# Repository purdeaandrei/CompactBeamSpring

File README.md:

# Compact Beamspring controller.

This controller only supports new style card edge connectors only, and it requires the side
of the card edge connector to be cut off, and the pins be bent 90 degress.

## Images

## Other controllers in this family:
* https://github.com/purdeaandrei/CompactBeamSpringAdditionalExpansion
* https://github.com/purdeaandrei/SMDModelFController
* https://github.com/purdeaandrei/SMDModelFController/tree/extra_columns
* https://github.com/purdeaandrei/SMD4704KishsaverClassModelFController
* https://github.com/listofoptions/TH-XWhatsIt

## Origins and license

This project is based on the Through-hole xwhatsit by listofoptions, which is un turn
based on the capsense controllers by XWhatsIt
(Tom Wong-Cornall). original liscencure holds, as well as CERN OSH
(compatible license).

original implementation of Tom Wong-Cornall's controller documented here

http://downloads.cornall.co/ibm-capsense-usb-web/ibm-capsense-usb.html

Working theory of operation is under the previous link.

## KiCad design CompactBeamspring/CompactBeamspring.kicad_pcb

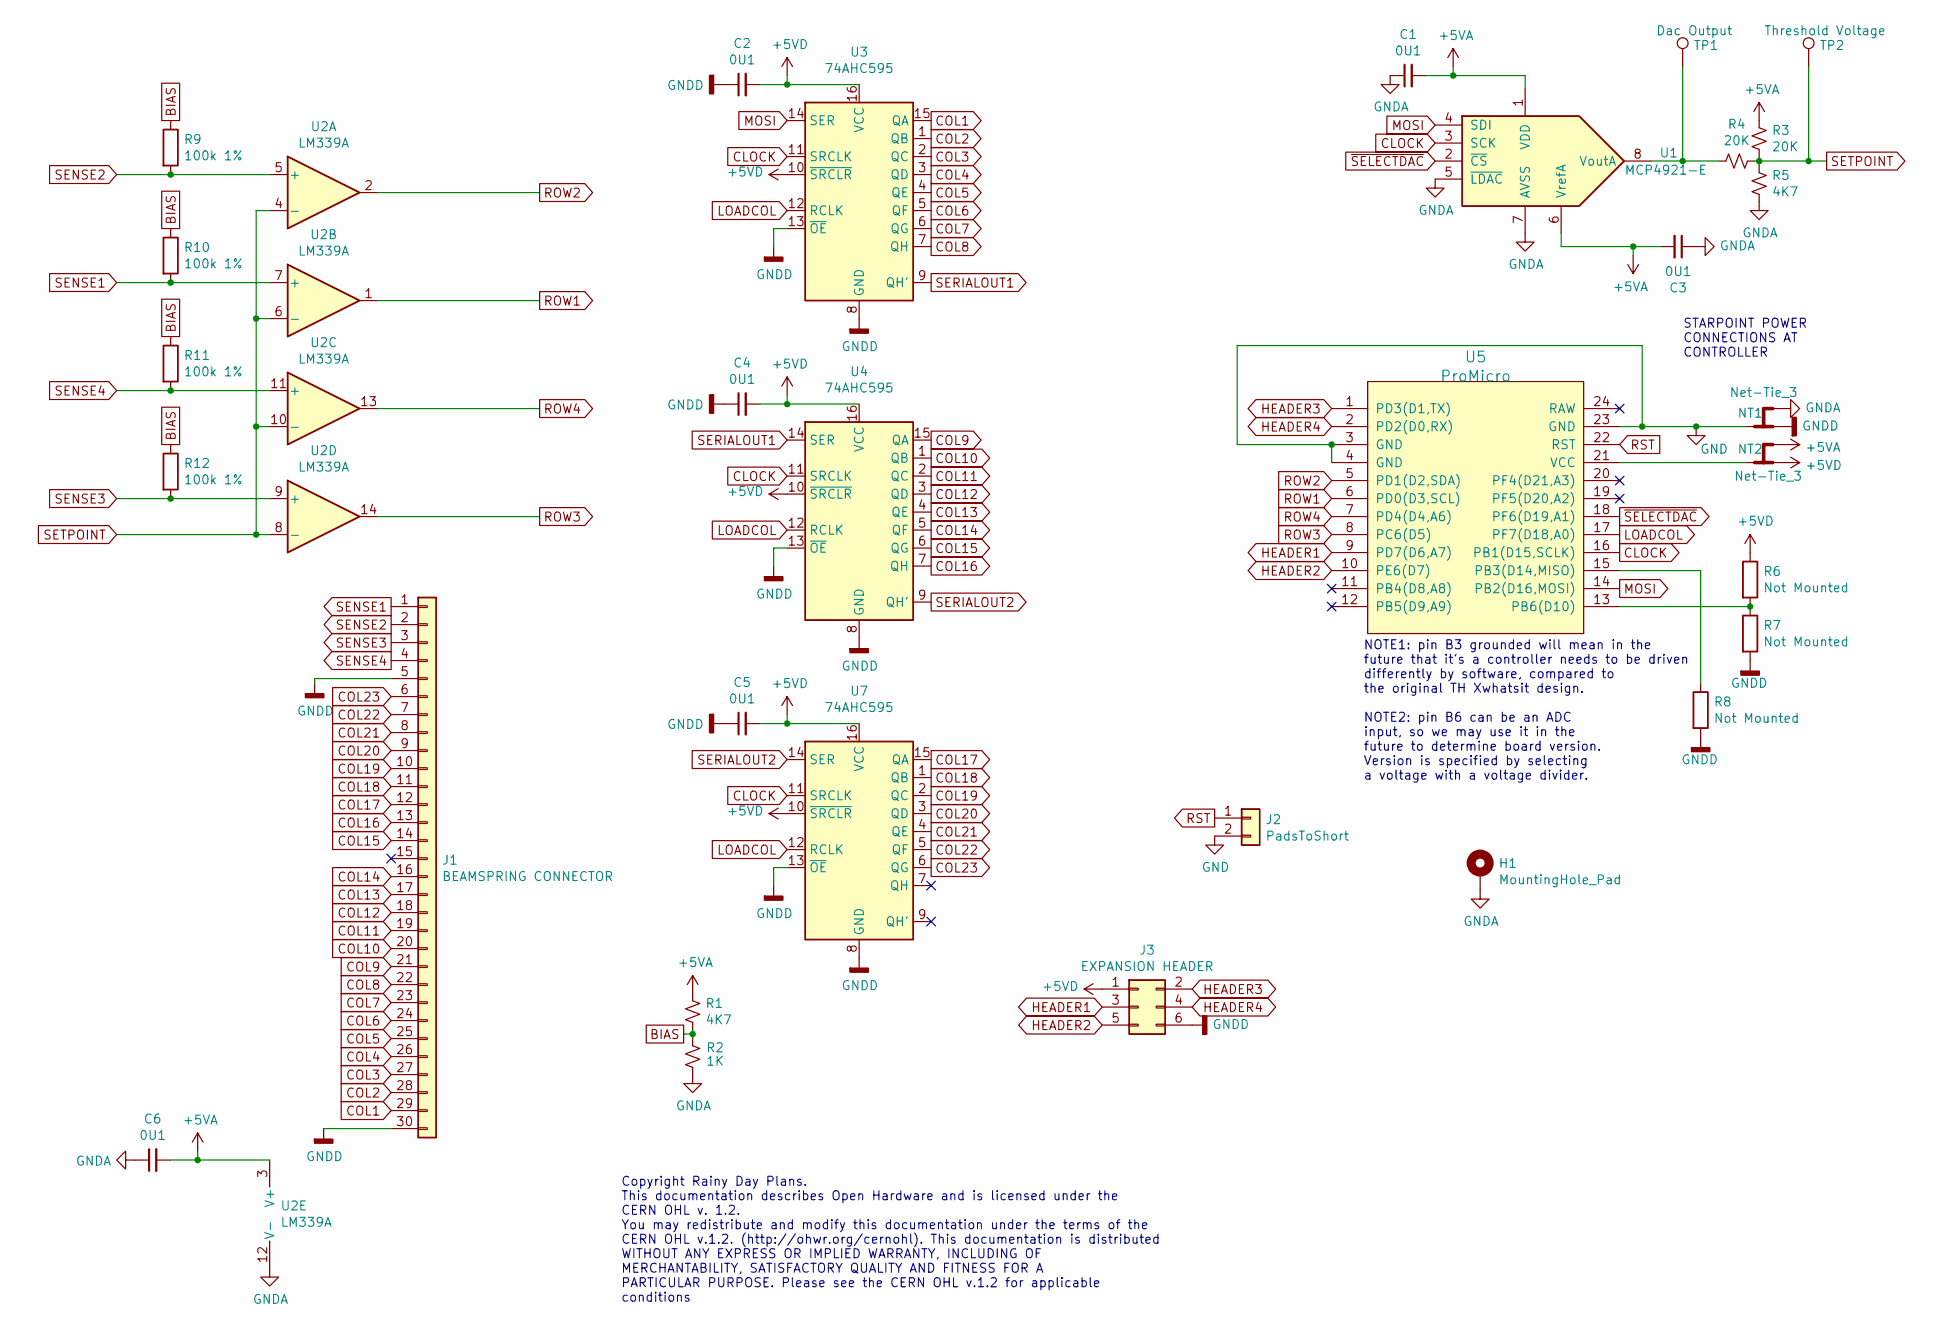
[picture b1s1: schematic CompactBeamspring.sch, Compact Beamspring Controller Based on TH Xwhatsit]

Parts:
C1, C2, C3, C4, C5, C6: 0U1; C_0805_2012Metric_Pad1.15x1.40mm_HandSolder; LCSC C49678
H1: MountingHole_Pad; ChassisGnd
J1: BEAMSPRING CONNECTOR; 30-pin-universal-beamspring-connector_v3_onlyflat
J2: PadsToShort
J3: EXPANSION HEADER; PinHeader_2x03_P2.54mm_Vertical
NT1, NT2: Net-Tie_3; NetTie-3_THT_Pad0.3mm
R1, R5: 4K7; R_0805_2012Metric_Pad1.15x1.40mm_HandSolder; LCSC C17673
R2: 1K; R_0805_2012Metric_Pad1.15x1.40mm_HandSolder; LCSC C17513
R3, R4: 20K; R_0805_2012Metric_Pad1.15x1.40mm_HandSolder; LCSC C4328
R6, R7, R8: Not Mounted; R_0805_2012Metric_Pad1.15x1.40mm_HandSolder
R9, R10, R11, R12: 100k 1%; R_0805_2012Metric_Pad1.15x1.40mm_HandSolder; LCSC C17407
TP1: Dac Output; TestPoint_Pad_D1.0mm
TP2: Threshold Voltage; TestPoint_Pad_D1.0mm
U1: MCP4921-E; SOIC-8_3.9x4.9mm_P1.27mm; LCSC C43499
U2: LM339A; SOIC-14_3.9x8.7mm_P1.27mm; LCSC C74559
U3, U4, U7: 74AHC595; SOIC-16_3.9x9.9mm_P1.27mm; LCSC C5520
U5: ProMicro

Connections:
+5VA: C1.2, C3.2, C6.2, NT2.3, R1.1, R3.2, U1.1 (VDD), U1.6 (VrefA), U2.3 (V+)
+5VD: C2.2, C4.2, C5.2, J3.1, NT2.1, R6.1, U3.10 (~SRCLR), U3.16 (VCC), U4.10 (~SRCLR), U4.16 (VCC), U7.10 (~SRCLR), U7.16 (VCC)
BIAS: R1.2, R2.2, R9.1, R10.1, R11.1, R12.1
CLOCK: U1.3 (SCK), U3.11 (SRCLK), U4.11 (SRCLK), U5.16 (PB1(D15,SCLK)), U7.11 (SRCLK)
COL1: J1.29, U3.15 (QA)
COL2: J1.28, U3.1 (QB)
COL3: J1.27, U3.2 (QC)
COL4: J1.26, U3.3 (QD)
COL5: J1.25, U3.4 (QE)
COL6: J1.24, U3.5 (QF)
COL7: J1.23, U3.6 (QG)
COL8: J1.22, U3.7 (QH)
COL9: J1.21, U4.15 (QA)
COL10: J1.20, U4.1 (QB)
COL11: J1.19, U4.2 (QC)
COL12: J1.18, U4.3 (QD)
COL13: J1.17, U4.4 (QE)
COL14: J1.16, U4.5 (QF)
COL15: J1.14, U4.6 (QG)
COL16: J1.13, U4.7 (QH)
COL17: J1.12, U7.15 (QA)
COL18: J1.11, U7.1 (QB)
COL19: J1.10, U7.2 (QC)
COL20: J1.9, U7.3 (QD)
COL21: J1.8, U7.4 (QE)
COL22: J1.7, U7.5 (QF)
COL23: J1.6, U7.6 (QG)
GND: J2.2, NT1.2, U5.3 (GND), U5.4 (GND), U5.23 (GND)
GNDA: C1.1, C3.1, C6.1, H1.1, NT1.3, R2.1, R5.1, U1.5 (~LDAC~), U1.7 (AVSS), U2.12 (V-)
GNDD: C2.1, C4.1, C5.1, J1.5, J1.30, J3.6, NT1.1, R7.2, R8.2, U3.8 (GND), U3.13 (~OE), U4.8 (GND), U4.13 (~OE), U7.8 (GND), U7.13 (~OE)
HEADER1: J3.3, U5.9 (PD7(D6,A7))
HEADER2: J3.5, U5.10 (PE6(D7))
HEADER3: J3.2, U5.1 (PD3(D1,TX))
HEADER4: J3.4, U5.2 (PD2(D0,RX))
LOADCOL: U3.12 (RCLK), U4.12 (RCLK), U5.17 (PF7(D18,A0)), U7.12 (RCLK)
MOSI: U1.4 (SDI), U3.14 (SER), U5.14 (PB2(D16,MOSI))
unnamed: NT2.2, U5.21 (VCC)
unnamed: R4.2, TP1.1, U1.8 (VoutA)
unnamed: R6.2, R7.1, U5.13 (PB6(D10))
unnamed: R8.1, U5.15 (PB3(D14,MISO))
ROW1: U2.1, U5.6 (PD0(D3,SCL))
ROW2: U2.2, U5.5 (PD1(D2,SDA))
ROW3: U2.14, U5.8 (PC6(D5))
ROW4: U2.13, U5.7 (PD4(D4,A6))
RST: J2.1, U5.22 (RST)
SENSE1: J1.1, R10.2, U2.7 (+)
SENSE2: J1.2, R9.2, U2.5 (+)
SENSE3: J1.3, R12.2, U2.9 (+)
SENSE4: J1.4, R11.2, U2.11 (+)
SERIALOUT1: U3.9 (QH'), U4.14 (SER)
SERIALOUT2: U4.9 (QH'), U7.14 (SER)
SETPOINT: R3.1, R4.1, R5.2, TP2.1, U2.4 (-), U2.6 (-), U2.8 (-), U2.10 (-)
~SELECTDAC: U1.2 (~CS~), U5.18 (PF6(D19,A1))

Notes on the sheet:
Copyright Rainy Day Plans. This documentation describes Open Hardware and is licensed under the CERN OHL v. 1.2. You may redistribute and modify this documentation under the terms of the CERN OHL v.1.2. (http://ohwr.org/cernohl). This documentation is distributed WITHOUT ANY EXPRESS OR IMPLIED WARR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
NOTE1: pin B3 grounded will mean in the future that it's a controller needs to be driven differently by software, compared to the original TH Xwhatsit design. NOTE2: pin B6 can be an ADC input, so we may use it in the future to determine board version. Version is specified by selecting a voltage wi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
STARPOINT POWER CONNECTIONS AT CONTROLLER

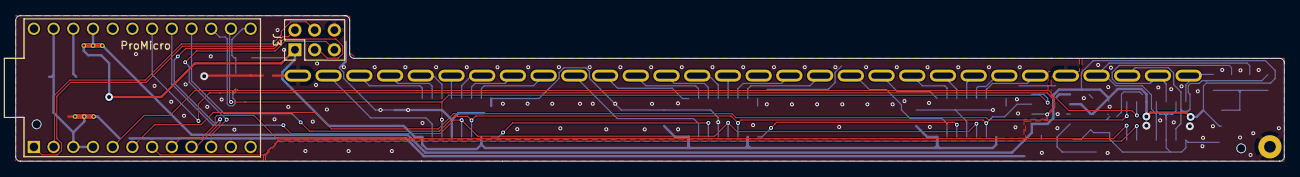
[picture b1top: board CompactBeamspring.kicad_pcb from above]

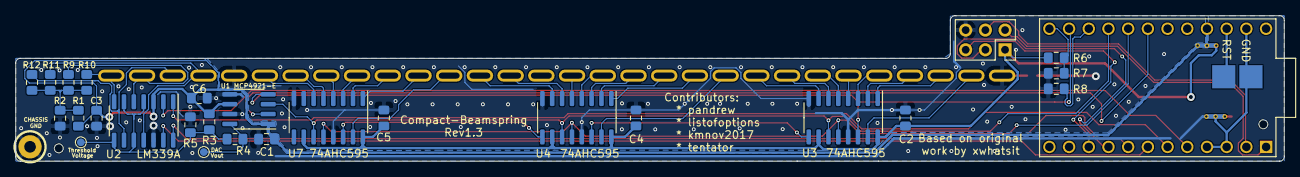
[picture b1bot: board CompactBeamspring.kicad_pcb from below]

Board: 2 copper layers, 163.6 x 18.8 mm, 32 parts (29 on the bottom side), 53 nets.

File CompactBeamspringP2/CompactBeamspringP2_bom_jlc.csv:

"Comment","Designator","Footprint","LCSC Part #"
"0U1","C2,C6,C5,C3,C1,C4","C_0805_2012Metric_Pad1.15x1.40mm_HandSolder","C49678"
"1K","R2","R_0805_2012Metric_Pad1.15x1.40mm_HandSolder","C17513"
"20K","R4,R3","R_0805_2012Metric_Pad1.15x1.40mm_HandSolder","C4328"
"4K7","R5,R1","R_0805_2012Metric_Pad1.15x1.40mm_HandSolder","C17673"
"100k 1%","R9,R10,R11,R12","R_0805_2012Metric_Pad1.15x1.40mm_HandSolder","C149504"
"MCP4921-E","U1","SOIC-8_3.9x4.9mm_P1.27mm","C43499"
"LM339A","U2","SOIC-14_3.9x8.7mm_P1.27mm","C74559"
"74AHC595","U3,U4,U7","SOIC-16_3.9x9.9mm_P1.27mm","C5520"

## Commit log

2020-08-16 Added compact beamspring-only version
2020-08-17 remove old gerber files
2020-08-17 added version selection resistor divider pads
2020-08-17 cleaned away some extra copper traces around pads connected to copper fills
2020-08-17 cleaned up cuts in the copper fill
2020-08-17 a bit more copper pour-related cleanups
2020-08-17 Added chassis ground, and added some silkscreen
2020-08-17 fixed net tie thermal relief
2020-08-17 moved chassis gnd connection a little in order to get 3 connections to gnd plane
2020-08-17 added copper fill keepout to shorted configuration resistor
2020-08-17 added forgotten chassis gnd footprint
2020-08-17 more tweaks: corners bigger radius, some more rework on traces, and copper fills
2020-08-17 added panelized pcb
2020-08-17 added tooling hole
2020-08-17 added tooling holes to existing panel
2020-08-17 single pcb: added tooling holes, position is only good for when pcbs are panelized back-to-back
2020-08-17 disable the keep upright feature on the single pcb, usefule for future panelizations
2020-08-17 rotate silkscreens into proper orientation on panel
2020-08-17 added lcsc part number to a bunch of components. Still todo: comparator and 74hc595
2020-08-18 added lcsc numbers for remaining chips, changed some silkscreen to match parts, removed stay-upright flag from all silkscreen, etc...
2020-08-18 added panelized gerbers, bom and cpl files
2020-08-18 rotated pro micro silkscreen
2020-08-18 added silkscreen for jlcpcb order number to panel
2020-08-18 panel: regenerated gerbers
2020-08-18 improved single board net tie to copper fill connection type
2020-08-18 single board: tightened up copper fill zones around board
2020-08-18 panel: tightened up and fixed copper fills, changed net tie to solid clearance
2020-08-18 beam_p_gerbers: regenerated
2020-08-19 single board: move RN farther away from resistor, hopefully resolving the too little soldering space warning from the assembly house
2020-08-19 removed old panel, will re-do now
2020-08-19 removed old plugboards left-over
2020-08-19 Renamed project to CompactBeamspring
2020-08-19 moved 3d component into libraries subfolder
2020-08-19 added pro micro 3d model
2020-08-19 make schematic point to the right 3d model
2020-08-19 added note
2020-08-19 added 2-board panel
2020-08-19 Added CompactBeamspringP1 1-piece panel to make smt assembly possible for low volumes
2020-08-19 Added auxiliary axis on the bottom left to both panels
2020-08-19 2-panel: added silkscreen for jlcpcb part number. 1-panel already has it
2020-08-19 Panels: added gerbers
2020-08-19 Added positioning csv files
2020-08-19 Fixed rotation and PosX of all components in JLCPCB positioning file
2020-08-19 made it th xwhatsit software compatible, added dac testpoints, added reset shorting pads, generally reworked to be nicer
2020-08-20 More mods
2020-08-20 Moved to individual resistors instead of resistor network, added a bit more space next to the promicro
2020-10-25 moved gerbers into zips to make it easier to order
2021-05-01 updated CHANGES.txt
2021-05-03 Updated Pro Micro schematic symbol, and added schematics
2021-10-30 Removed proprietary datasheets
2021-10-30 Clarify license of card edge model
2021-10-30 Clarified license of the footprint library
2021-10-30 Pro Micro 3D Model: include pins
2021-10-30 Beamspring footprint: Move custom modifications back into footprint library item.
2021-10-30 Fixup wrong footprint reference
2021-10-30 Updated Pro Micro and solenoid header footprint for more correct rendering
2021-10-30 Added rendered images, tweaked readme
2022-02-14 Update component rotations, to match new behaviour of JLCPCB on the bottom layer
2022-07-31 Updated 100k resistor LCSC part numbers
2022-07-31 Updated shift register LCSC part number
2022-07-31 fix rotations to match latest JLCPCB behaviour
2022-09-15 Revert "Updated shift register LCSC part number"
    This reverts commit 109b71d9faab148fe864110445be2db0dc0f59e0.

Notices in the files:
CompactBeamspring/CompactBeamspring.kicad_pcb:
Licenced under CERN OHL Version 1.2
